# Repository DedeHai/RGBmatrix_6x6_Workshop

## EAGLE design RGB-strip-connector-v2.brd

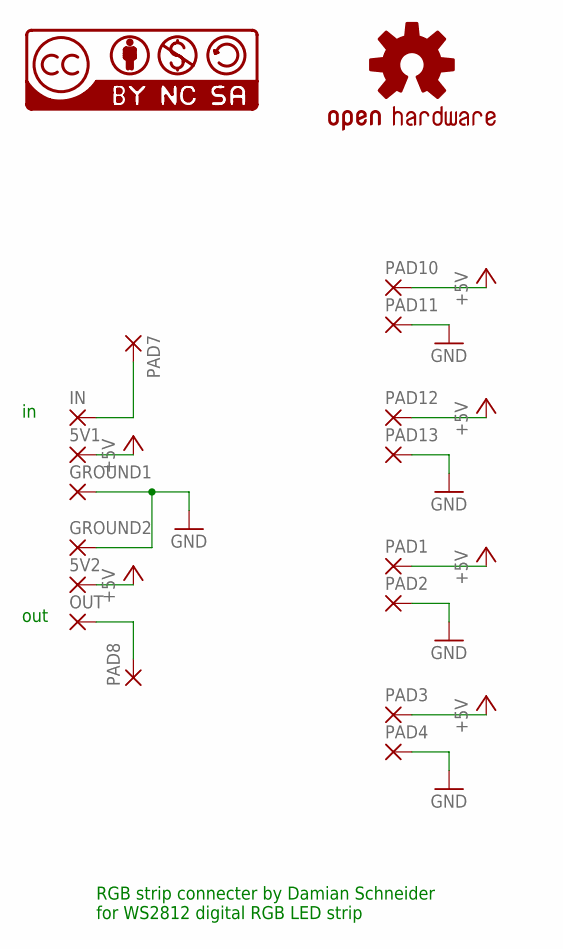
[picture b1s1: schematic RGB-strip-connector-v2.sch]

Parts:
5V1, 5V2: SMD2; SMD1,27-2,54
GROUND1, GROUND2: SMD2; SMD1,27-2,54
IN: SMD2; SMD1,27-2,54
LOGO1: OSHW-LOGOL; OSHW-LOGO-L
OUT: SMD2; SMD1,27-2,54
PAD1, PAD2, PAD3, PAD4, PAD10, PAD11, PAD12, PAD13: SMD5; SMD2,54-5,08
PAD7, PAD8: SMD2; SMD1,27-2,54
U$1: CC-NC-BCNIX; CC-NC-B_NIX

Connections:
+5V: 5V1.1, 5V2.1, PAD1.1, PAD3.1, PAD10.1, PAD12.1
GND: GROUND1.1, GROUND2.1, PAD2.1, PAD4.1, PAD11.1, PAD13.1
unnamed: OUT.1, PAD8.1
unnamed: IN.1, PAD7.1

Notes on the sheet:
out
RGB strip connecter by Damian Schneider for WS2812 digital RGB LED strip

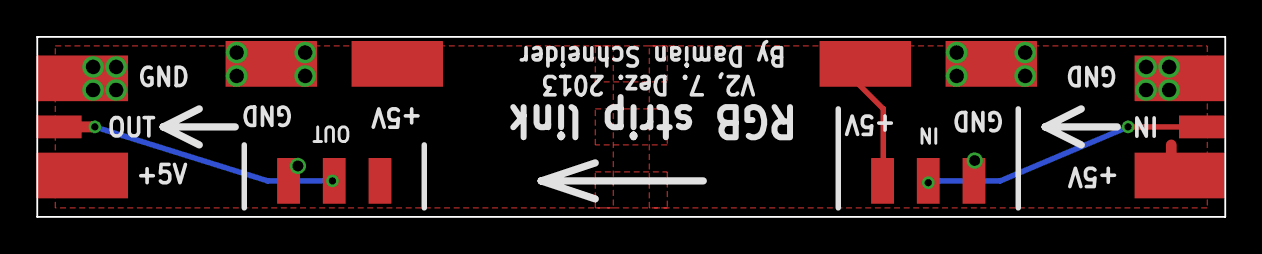
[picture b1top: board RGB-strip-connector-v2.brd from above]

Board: 2 copper layers, 66.0 x 10.0 mm, 18 parts (1 on the bottom side), 4 nets.

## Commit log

2015-04-11 Initial release
    Software release for the Workshop at FabLab Winterthur. Demonstrates
    all hardware and software functions and does some nice animations. Code
    optimized for 6x6 pixels.
2015-04-11 Reorganized Folder Structure, Added libraries
2015-04-11 Initial Release
2015-04-11 Clarified license
2015-04-19 Bugfixes
2015-04-19 Microscope Image
2015-05-16 Added randomize option
    if option is activated (uncomment the RANDOMCHANGEINTERVAL definition)
    the program will change to a random program after each interval.
2015-05-16 bugfix
2016-03-04 test
2016-03-05 minor tweaks
2016-03-18 add SVG file
2016-03-18 added svg laser file
2016-03-27 updated anleitung
2016-03-27 added aufhänger
2016-12-30 adding 3x2 pixel matrix code

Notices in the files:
parts and their libraries:
SparkFun-Aesthetics: Licensing: Creative Commons ShareAlike 4.0 International - https://creativecommons.org/licenses/by-sa/4.0
cc-by-nc-sa: All hardware is licensed under the Creative Commons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
